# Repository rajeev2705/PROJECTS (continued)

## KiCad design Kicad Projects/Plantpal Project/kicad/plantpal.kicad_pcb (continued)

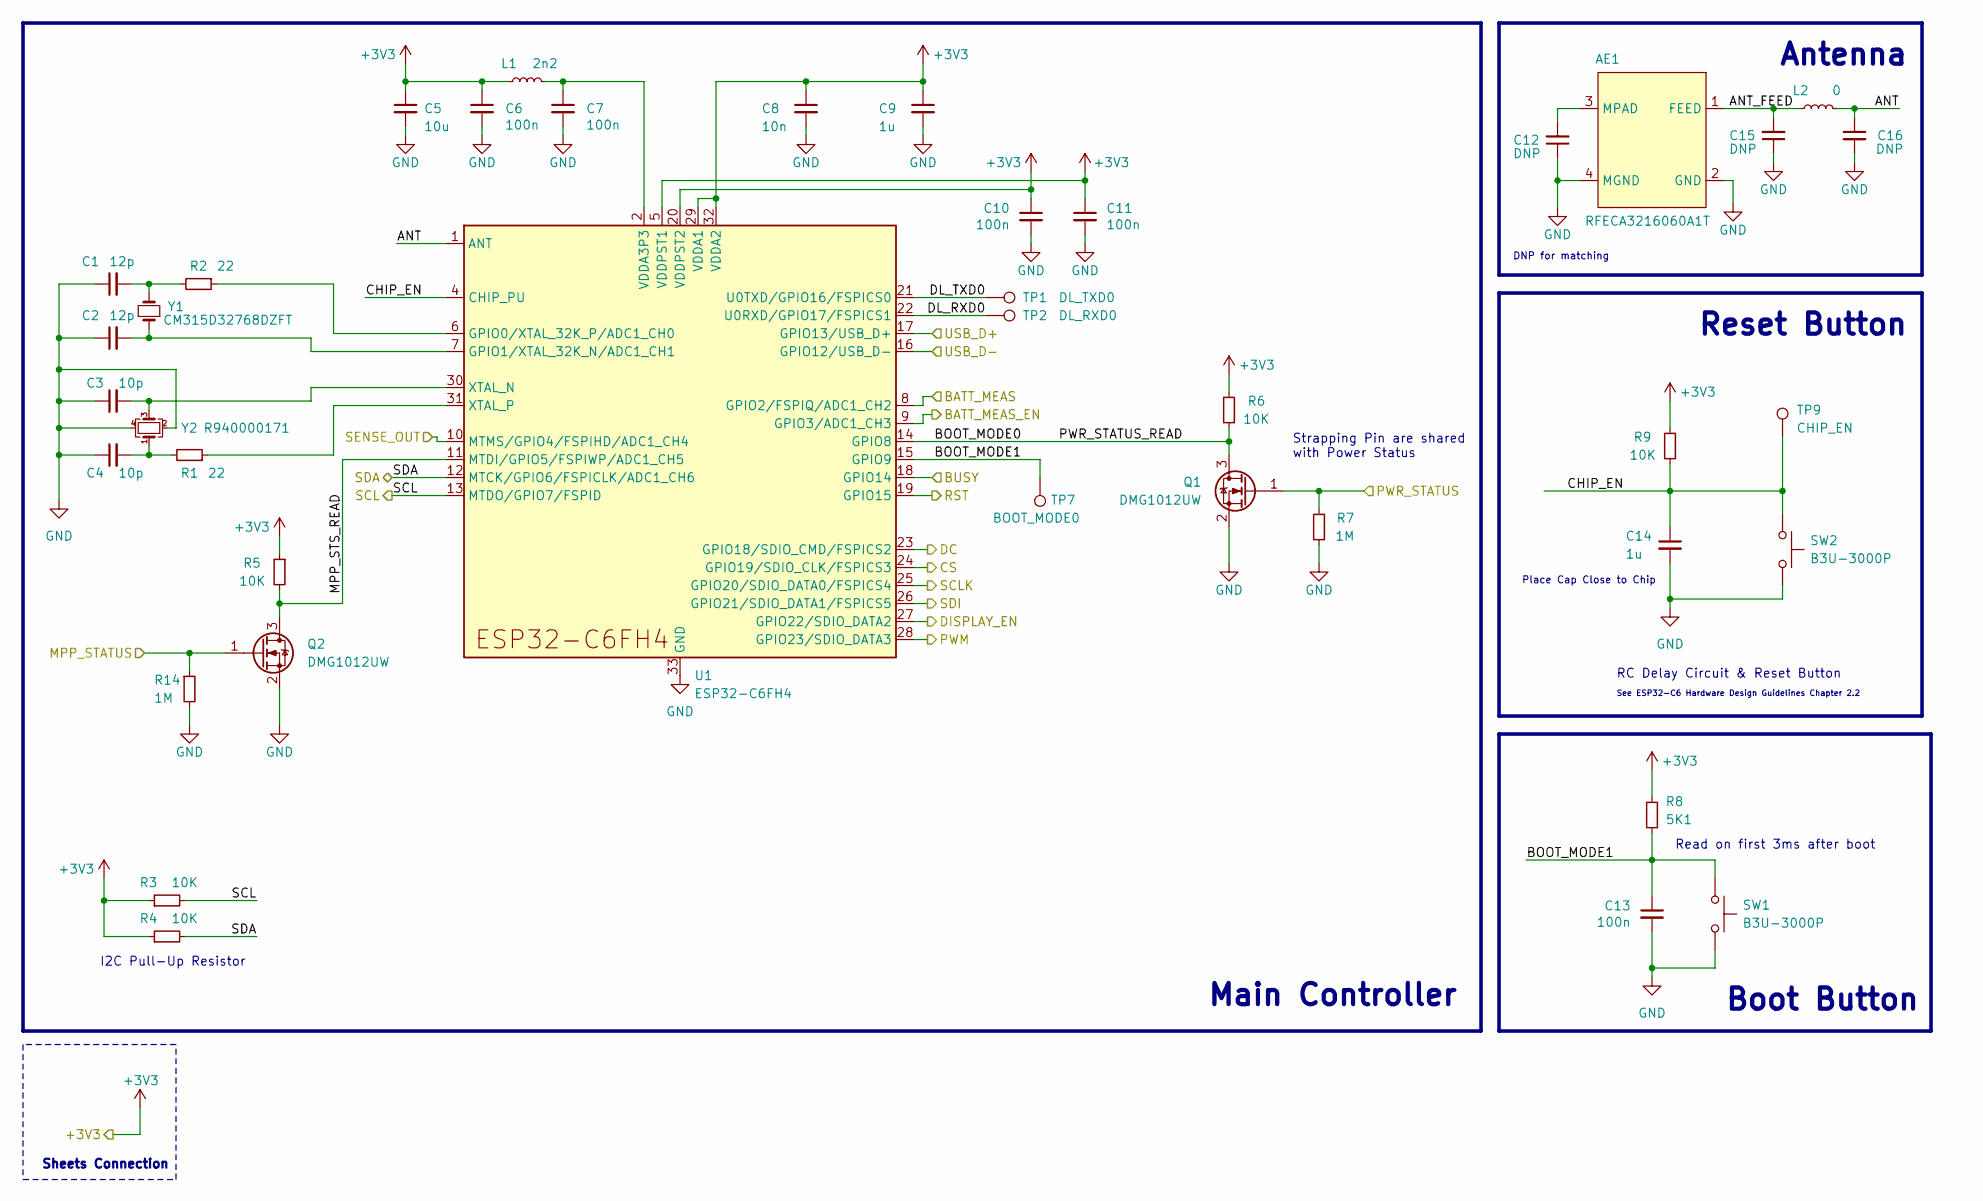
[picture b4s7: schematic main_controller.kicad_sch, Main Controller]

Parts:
AE1: RFECA3216060A1T; Part Description Chip RF Antenna 2.4GHz 2dBi
C1, C2: 12p; C_0402_1005Metric; Part Description Ceramic Capacitors 50V 12pF C0G ±1%
C3, C4: 10p; C_0402_1005Metric; Part Description Ceramic Capacitors 50V 10pF C0G ±1%
C5: 10u; C_0603_1608Metric; Part Description Ceramic Capacitor 10V 10uF X5R ±10% 0603
C6, C7, C10, C11, C13: 100n; C_0402_1005Metric; Part Description Ceramic Capacitor 16V 100nF X7R ±10%
C8: 10n; C_0402_1005Metric; Part Description Ceramic Capacitors 16V 10nF X7R ±10%
C9, C14: 1u; C_0402_1005Metric; Part Description Ceramic Capacitors 10V 1uF X7R ±10%
C12, C15, C16: DNP; C_0402_1005Metric
L1: 2n2; L_0402_1005Metric; Part Description Power Inductors 2.53A 2.2nH ±2%
L2: 0; L_0402_1005Metric; Part Description Resistor 62.5mW ±1% 0Ω
Q1, Q2: DMG1012UW; SOT-323_SC-70; Part Description MOSFET N Channel 20V 1A 450mΩ@4.5V,600m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
R1, R2: 22; R_0402_1005Metric; Part Description Resistor 62.5mW ±1% 22Ω
R3, R4, R5, R6, R9: 10K; R_0402_1005Metric; Part Description Resistors 62.5mW ±1% 10kΩ
R7, R14: 1M; R_0402_1005Metric; Part Description Resistor 62.5mW ±1% 1MΩ
R8: 5K1; R_0402_1005Metric; Part Description Resistor 62.5mW ±1% 5.1kΩ
SW1, SW2: B3U-3000P; SW_SPST_B3U-3000P; Part Description Tactile Switches NO 50mA 100MΩ 12V 1.59N
TP1: DL_TXD0; TestPoint_Pad_D1.0mm
TP2: DL_RXD0; TestPoint_Pad_D1.0mm
TP7: BOOT_MODE0; TestPoint_Pad_D1.0mm
TP9: CHIP_EN; TestPoint_Pad_D1.0mm
U1: ESP32-C6FH4; QFN-32-1EP_5x5mm_P0.5mm_EP3.6x3.6mm; Part Description Wireless SOC Bluetooth, WiFi Bluetooth 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
Y1: CM315D32768DZFT; Crystal_SMD_3215-2Pin_3.2x1.5mm; Part Description Crystals 32.768kHz 12.5pF ±20ppm
Y2: R940000171; Crystal_SMD_2016-4Pin_2.0x1.6mm; Part Description Crystals 40MHz 9pF ±10ppm

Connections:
+3V3: C5.1, C6.1, C8.1, C9.1, C10.1, C11.1, L1.1, R3.1, R4.1, R5.1, R6.1, R8.2, R9.1, U1.5 (VDDPST1), U1.20 (VDDPST2), U1.29 (VDDA1), U1.32 (VDDA2); also elsewhere on the board
/Display/BUSY: U1.18 (GPIO14); also elsewhere on the board
/Display/CS: U1.24 (GPIO19/SDIO_CLK/FSPICS3); also elsewhere on the board
/Display/DC: U1.23 (GPIO18/SDIO_CMD/FSPICS2); also elsewhere on the board
/Display/RST: U1.19 (GPIO15); also elsewhere on the board
/Display/SCLK: U1.25 (GPIO20/SDIO_DATA0/FSPICS4); also elsewhere on the board
/Display/SDI: U1.26 (GPIO21/SDIO_DATA1/FSPICS5); also elsewhere on the board
/Main Controller/ANT: C16.1, L2.2, U1.1 (ANT)
/Main Controller/ANT_FEED: AE1.1 (FEED), C15.2, L2.1
/Main Controller/BATT_MEAS: U1.8 (GPIO2/FSPIQ/ADC1_CH2); also elsewhere on the board
/Main Controller/BATT_MEAS_EN: U1.9 (GPIO3/ADC1_CH3); also elsewhere on the board
/Main Controller/BOOT_MODE0: Q1.3 (D), R6.2, U1.14 (GPIO8)
/Main Controller/BOOT_MODE1: C13.1, R8.1, SW1.1, TP7.1, U1.15 (GPIO9)
/Main Controller/CHIP_EN: C14.1, R9.2, SW2.1, TP9.1, U1.4 (CHIP_PU)
/Main Controller/DISPLAY_EN: U1.27 (GPIO22/SDIO_DATA2); also elsewhere on the board
/Main Controller/DL_RXD0: TP2.1, U1.22 (U0RXD/GPIO17/FSPICS1)
/Main Controller/DL_TXD0: TP1.1, U1.21 (U0TXD/GPIO16/FSPICS0)
/Main Controller/MPP_STATUS: Q2.1 (G), R14.1; also elsewhere on the board
/Main Controller/MPP_STS_READ: Q2.3 (D), R5.2, U1.11 (MTDI/GPIO5/FSPIWP/ADC1_CH5)
/Main Controller/PWM: U1.28 (GPIO23/SDIO_DATA3); also elsewhere on the board
/Main Controller/PWR_STATUS: Q1.1 (G), R7.1; also elsewhere on the board
/Main Controller/SENSE_OUT: U1.10 (MTMS/GPIO4/FSPIHD/ADC1_CH4); also elsewhere on the board
/Main Controller/USB_D+: U1.17 (GPIO13/USB_D+); also elsewhere on the board
/Main Controller/USB_D-: U1.16 (GPIO12/USB_D-); also elsewhere on the board
/SCL: R3.2, U1.13 (MTDO/GPIO7/FSPID); also elsewhere on the board
/SDA: R4.2, U1.12 (MTCK/GPIO6/FSPICLK/ADC1_CH6); also elsewhere on the board
GND: AE1.2 (GND), AE1.4 (MGND), C1.1, C2.1, C3.1, C4.1, C5.2, C6.2, C7.2, C8.2, C9.2, C10.2, C11.2, C12.1, C13.2, C14.2, C15.1, C16.2, Q1.2 (S), Q2.2 (S), R7.2, R14.2, SW1.2, SW2.2, U1.33 (GND), Y2.2, Y2.4; also elsewhere on the board
unnamed: AE1.3 (MPAD), C12.2
unnamed: C1.2, R2.2, Y1.2
unnamed: C4.2, R1.2, Y2.1
unnamed: C7.1, L1.2, U1.2 (VDDA3P3), U1.3 (VDDA3P3)
unnamed: R2.1, U1.6 (GPIO0/XTAL_32K_P/ADC1_CH0)
unnamed: C2.2, U1.7 (GPIO1/XTAL_32K_N/ADC1_CH1), Y1.1
unnamed: C3.2, U1.30 (XTAL_N), Y2.3
unnamed: R1.1, U1.31 (XTAL_P)

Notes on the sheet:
Place Cap Close to Chip
Reset Button
Antenna
DNP for matching
Main Controller
Sheets Connection
Boot Button
See ESP32-C6 Hardware Design Guidelines Chapter 2.2
RC Delay Circuit & Reset Button
Read on first 3ms after boot
I2C Pull-Up Resistor
Strapping Pin are shared with Power Status

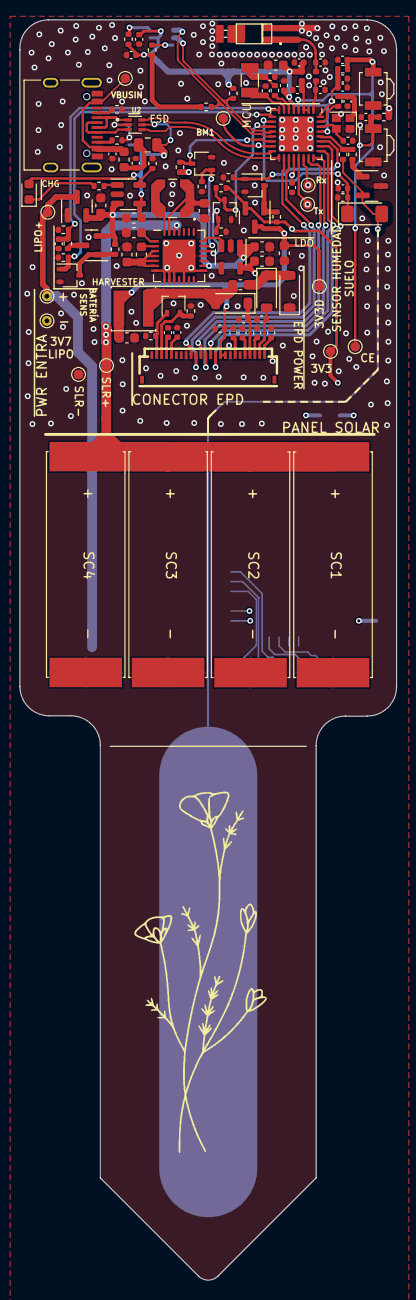
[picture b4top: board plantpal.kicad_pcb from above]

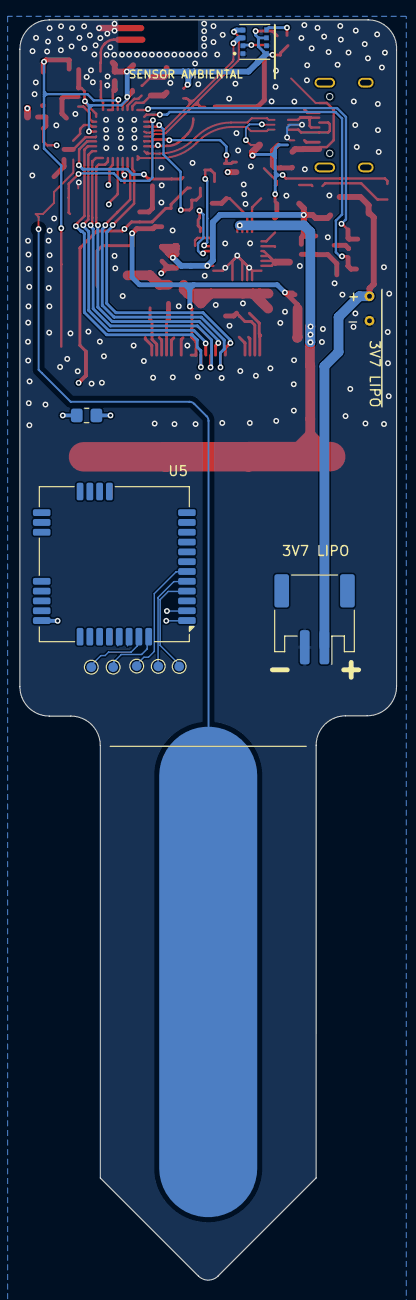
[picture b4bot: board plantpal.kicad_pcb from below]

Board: 4 copper layers, 38.4 x 128.5 mm, 125 parts (8 on the bottom side), 74 nets.

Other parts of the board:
TP12, TP13, TP14, TP15, TP16: TestPoint_Pad_D1.0mm
U5: RAK3172

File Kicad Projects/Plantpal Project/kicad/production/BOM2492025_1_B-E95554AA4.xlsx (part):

BOM File: |  | BOM2492025_1 |  |  |  |  |  |  | Order ID： | B-E95554AA4 |  |  |  | Quote Time: | 2025/09/25 09:05:02
Purchase Quantity： |  | 2 pcs |  |  |  |  |  |  | BOM Total ($)： | 129.17
Inquiry |  |  |  |  |  |  |  |  | HQNextPCB-Quotation
S/N | Designator* | Quantity* | Manufacturer Part Number* | Manufacturer | Package /Footprint | Description | Procurement Type | Customer Note | Quote MPN | Quote Brand | Package /Footprint | Plan Qty | Overage Amount | Quote Qty | Unit Price($) | Subtotal($) | Lead Time | Question from HQ NextPCB | Customer Reply
1 | AE1 | 1 | RFECA3216060A1T | Walsin Technology Corporation | RFECA3216060A1T | RFECA3216060A1T |  |  | RFECA3216060A1T | Walsin | ANT_3.1X1.6MM | 2 | 15 | 17 | 3.5150000000000001E-2 | 0.6 | In Stock
2 | BT1 | 1 | S2B-PH-SM4-TB(LF)(SN) | JST Sales America | JST_PH_S2B-PH-SM4-TB_1x02-1MP_P2.00mm_Horizontal | S2B-PH-SM4-TB(LF)(SN) |  |  | S2B-PH-SM4-TB(LF)(SN) | JST | Accessories_7.9X7.6MM_SM | 2 | 3 | 5 | 0.14524000000000001 | 0.73 | In Stock
3 | C1, C2 | 2 | GCM1555C1H120FA16D | Murata Electronics | 0402_1005Metric | 12p |  |  | GCM1555C1H120FA16D | Murata | 0402 | 4 | 50 | 54 | 7.8100000000000001E-3 | 0.42 | In Stock
4 | C3, C4 | 2 | GRM1555C1H100FA01D | Murata Electronics | 0402_1005Metric | 10p |  |  | GRM1555C1H100FA01D | Murata | 0402 | 4 | 50 | 54 | 8.0599999999999995E-3 | 0.44 | In Stock
5 | C5, C19, C20, C23, C24, C25, C26 | 7 | CL10A106KP8NNNC | Samsung Electro-Mechanics | 0603_1608Metric | 10u |  |  | CL10A106KP8NNNC | Samsung | 0603 | 14 | 40 | 54 | 4.7499999999999999E-3 | 0.26 | In Stock
6 | C6, C7, C10, C11, C13, C27, C28, C29 | 8 | CL05B104KO5NNNC | Samsung Electro-Mechanics | 0402_1005Metric | 100n |  |  | CL05B104KO5NNNC | Samsung | 0402 | 16 | 50 | 100 | 8.4999999999999995E-4 | 0.09 | In Stock
7 | C8 | 1 | CC0402KRX7R7BB103 | YAGEO | 0402_1005Metric | 10n |  |  | CC0402KRX7R7BB103 | Yageo | 0402 | 2 | 50 | 100 | 6.6E-4 | 7.0000000000000007E-2 | In Stock
8 | C9, C14, C31, C32, C33, C34, C35, C36, C37, C38, C39 | 11 | GRM155Z71A105KE01D | Murata Electronics | 0402_1005Metric | 1u |  |  | GRM155Z71A105KE01D | Murata | 0402 | 22 | 50 | 72 | 1.2030000000000001E-2 | 0.87 | In Stock
9 | C17 | 1 | CC0402KRX7R7BB103 | YAGEO | 0402_1005Metric | 10n |  |  | CC0402KRX7R7BB103 | Yageo | 0402 | 2 | 50 | 100 | 6.6E-4 | 7.0000000000000007E-2 | In Stock
10 | C18 | 1 | CL05B104KO5NNNC | Samsung Electro-Mechanics | 0402_1005Metric | 100n |  |  | CL05B104KO5NNNC | Samsung | 0402 | 2 | 50 | 100 | 8.4999999999999995E-4 | 0.09 | In Stock
11 | C21, C22 | 2 | GRM188R61A226ME15D | Murata Electronics | 0603_1608Metric | 22u |  |  | GRM188R61A226ME15D | Murata | 0603 | 4 | 40 | 100 | 1.2370000000000001E-2 | 1.24 | In Stock
12 | C30 | 1 | CL05B102KB5NNNC | Samsung Electro-Mechanics | 0402_1005Metric | 1n |  |  | CL05B102KB5NNNC | Samsung | 0402 | 2 | 50 | 52 | 8.7000000000000001E-4 | 0.05 | In Stock
13 | C40, C41 | 2 | CL10A475KA8NQNC | Samsung Electro-Mechanics | 0603_1608Metric | 4u7 |  |  | CL10A475KA8NQNC | Samsung | 0603 | 4 | 40 | 44 | 1.255E-2 | 0.55000000000000004 | In Stock
14 | D1 | 1 | VLMO1300-GS08 | Vishay Intertech | 0603_1608Metric | VLMO1300-GS08 |  |  | VLMO1300-GS08 | Vishay Semiconductors | 0603 | 2 | 15 | 17 | 0.16650000000000001 | 2.83 | 7-18 Days
15 | D3 | 1 | LL4148 | ST(Semtech) | MiniMELF | LL4148 |  |  | LL4148 | YONGYUTAI | SOD80 | 2 | 15 | 17 | 4.3400000000000001E-3 | 7.0000000000000007E-2 | In Stock
16 | D4, D5, D6 | 3 | MBR0530T1G | onsemi | SOD-123 | MBR0530 |  |  | MBR0530T1G | ON | SOD-123 | 6 | 30 | 36 | 2.826E-2 | 1.02 | In Stock
17 | F1 | 1 | SMD0805P075TF | RUILON(Shenzhen Ruilongyuan Elec) | 0805_2012Metric | 0.75A |  |  | SMD0805P075TF | RUILON(瑞隆源) | 0805 | 2 | 15 | 17 | 8.1909999999999997E-2 | 1.39 | 4-7 Days
18 | FB1 | 1 | MMZ1608B601CTAH0 | TDK | 0603_1608Metric | MMZ1608B601CTAH0 |  |  | MMZ1608B601CTAH0 | TDK | 0603 | 2 | 40 | 42 | 1.1730000000000001E-2 | 0.49 | In Stock
19 | J1 | 1 | U262-161N-4BVC11 | XKB Connectivity | XKB_U262-16XN-4BVC11 | U262-161N-4BVC11 |  |  | U262-161N-4BVC11 | XKB | SMD | 2 | 3 | 5 | 0.24346000000000001 | 1.22 | In Stock
20 | J4 | 1 | HC-FPC-05-09-24RLTAG | HCTL | FPC-SMD_24P-P0.50_HC-FPC-05-09-24RLTAG | HC-FPC-05-09-24RLTAG |  |  | HC-FPC-05-09-24RLTAG | HCTL | SMD,P=0.5mm,卧贴 | 2 | 3 | 5 | 0.14030000000000001 | 0.7 | In Stock
21 | L1 | 1 | LQW15AN2N2G80D | Murata Electronics | 0402_1005Metric | 2n2 |  |  | LQW15AN2N2G80D | muRata(村田) | 0402 | 2 | 40 | 42 | 6.3049999999999995E-2 | 2.65 | 4-7 Days
22 | L2 | 1 | 0402WGF0000TCE | UNI-ROYAL(Uniroyal Elec) | 0402_1005Metric |  |  |  | 0402WGF0000TCE | Uniohm | 0402 | 2 | 50 | 100 | 3.1E-4 | 0.03 | In Stock
23 | L3 | 1 | LPS4012-103MRC | Coilcraft | LPS4012-103MRB | 10u 0.55A |  |  | LPS4012-103MRC | Coilcraft(线艺) | SMD,3.9x3.9mm | 2 | 2 | 4 | 0.64856000000000003 | 2.59 | 4-7 Days
24 | L4 | 1 | MLZ1608M100WT000 | TDK | 0603_1608Metric | 10u |  |  | MLZ1608M100WT000 | TDK | 0603 | 2 | 30 | 32 | 3.5150000000000001E-2 | 1.1200000000000001 | In Stock
25 | L5 | 1 | FNR4012S100MT | cjiang (Changjiang Microelectronics Tech) | FNR4012S | 10u 1A |  |  | FNR4012S100MT | cjiang(长江微电) | 4012 | 2 | 5 | 10 | 5.6829999999999999E-2 | 0.56999999999999995 | 4-7 Days
26 | Q1, Q2, Q5, Q9 | 4 | DMG1012UW-7 | Diodes Incorporated | SOT-323_SC-70 | DMG1012UW |  |  | DMG1012UW-7 | DIODES | SOT-323 | 8 | 15 | 23 | 3.4430000000000002E-2 | 0.79 | In Stock
27 | Q3 | 1 | MMBT3906 2A | Jiangsu Changjing Electronics Technology Co., Ltd. | SOT-23 | MMBT3906 |  |  | MMBT3906 2A | TDSEMIC | SOT-23 | 2 | 15 | 50 | 3.0100000000000001E-3 | 0.15 | In Stock
28 | Q4, Q8 | 2 | PMV32UP | TECH PUBLIC | SOT-23 | PMV32UP |  |  | PMV32UP | TECH PUBLIC(台舟) | SOT-23 | 4 | 10 | 14 | 8.9779999999999999E-2 | 1.26 | 4-7 Days
29 | Q6 | 1 | AO3407A | Alpha & Omega Semicon | SOT-23 | AO3407A |  |  | AO3407A | BY | SOT23-3 | 2 | 15 | 17 | 2.554E-2 | 0.43 | In Stock
30 | Q7 | 1 | SI1308EDL-T1-GE3 | Vishay Intertech | SOT-323_SC-70 | SI1308EDL |  |  | SI1308EDL-T1-GE3 | Vishay | SOT-323 | 2 | 10 | 12 | 0.11650000000000001 | 1.4 | In Stock
31 | R1, R2 | 2 | 0402WGF220JTCE | UNI-ROYAL(Uniroyal Elec) | R_0402_1005Metric | 22 |  |  | 0402WGF220JTCE | Uniohm | 0402 | 4 | 50 | 100 | 3.1E-4 | 0.03 | In Stock
32 | R3, R4, R5, R6, R9, R16, R17, R18, R19, R21 | 10 | 0402WGF1002TCE | UNI-ROYAL(Uniroyal Elec) | R_0402_1005Metric | 10K |  |  | 0402WGF1002TCE | Uniohm | 0402 | 20 | 50 | 100 | 3.3E-4 | 0.03 | In Stock
33 | R7, R14, R22, R23, R24, R26, R28, R29 | 8 | 0402WGF1004TCE | UNI-ROYAL(Uniroyal Elec) | R_0402_1005Metric | 1M |  |  | 0402WGF1004TCE | Uniohm | 0402 | 16 | 50 | 100 | 2.9999999999999997E-4 | 0.03 | In Stock
34 | R8, R10, R11 | 3 | 0402WGF5101TCE | UNI-ROYAL(Uniroyal Elec) | R_0402_1005Metric | 5K1 |  |  | 0402WGF5101TCE | Uniohm | 0402 | 6 | 50 | 100 | 2.9E-4 | 0.03 | In Stock
35 | R12 | 1 | 0402WGF2001TCE | UNI-ROYAL(Uniroyal Elec) | R_0402_1005Metric | 2K |  |  | 0402WGF2001TCE | Uniohm | 0402 | 2 | 50 | 100 | 3.3E-4 | 0.03 | In Stock
36 | R13 | 1 | 0402WGF1001TCE | UNI-ROYAL(Uniroyal Elec) | R_0402_1005Metric | 1K |  |  | 0402WGF1001TCE | Uniohm | 0402 | 2 | 50 | 100 | 3.4000000000000002E-4 | 0.03 | In Stock
37 | R20 | 1 | 0402WGF4701TCE | UNI-ROYAL(Uniroyal Elec) | R_0402_1005Metric | 4K7 |  |  | 0402WGF4701TCE | Uniohm | 0402 | 2 | 50 | 100 | 3.3E-4 | 0.03 | In Stock
38 | R25 | 1 | RCWE0402R470FKEA | Vishay Intertech | R_0402_1005Metric | 470m |  |  | RCWE0402R470FKEA | Vishay / Dale | 0402 | 2 | 35 | 37 | 0.14219000000000001 | 5.26 | 7-18 Days
39 | SC1, SC2, SC3, SC4 | 4 | KXOB25-05X3F-TR | ANYSOLAR Ltd | KXOB25-05X3F-TR | KXOB25-05X3F-TR |  |  | KXOB25-05X3F-TR | ANYSOLAR Ltd | SMD_8X23 | 8 | 1 | 9 | 4.0199999999999996 | 36.18 | 7-18 Days
40 | SW1, SW2 | 2 | B3U-3000P | Omron Electronics | B3U-3000P | B3U-3000P |  |  | B3U-3000P | OMRON | SMD | 4 | 3 | 7 | 0.13292000000000001 | 0.93 | 4-7 Days
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
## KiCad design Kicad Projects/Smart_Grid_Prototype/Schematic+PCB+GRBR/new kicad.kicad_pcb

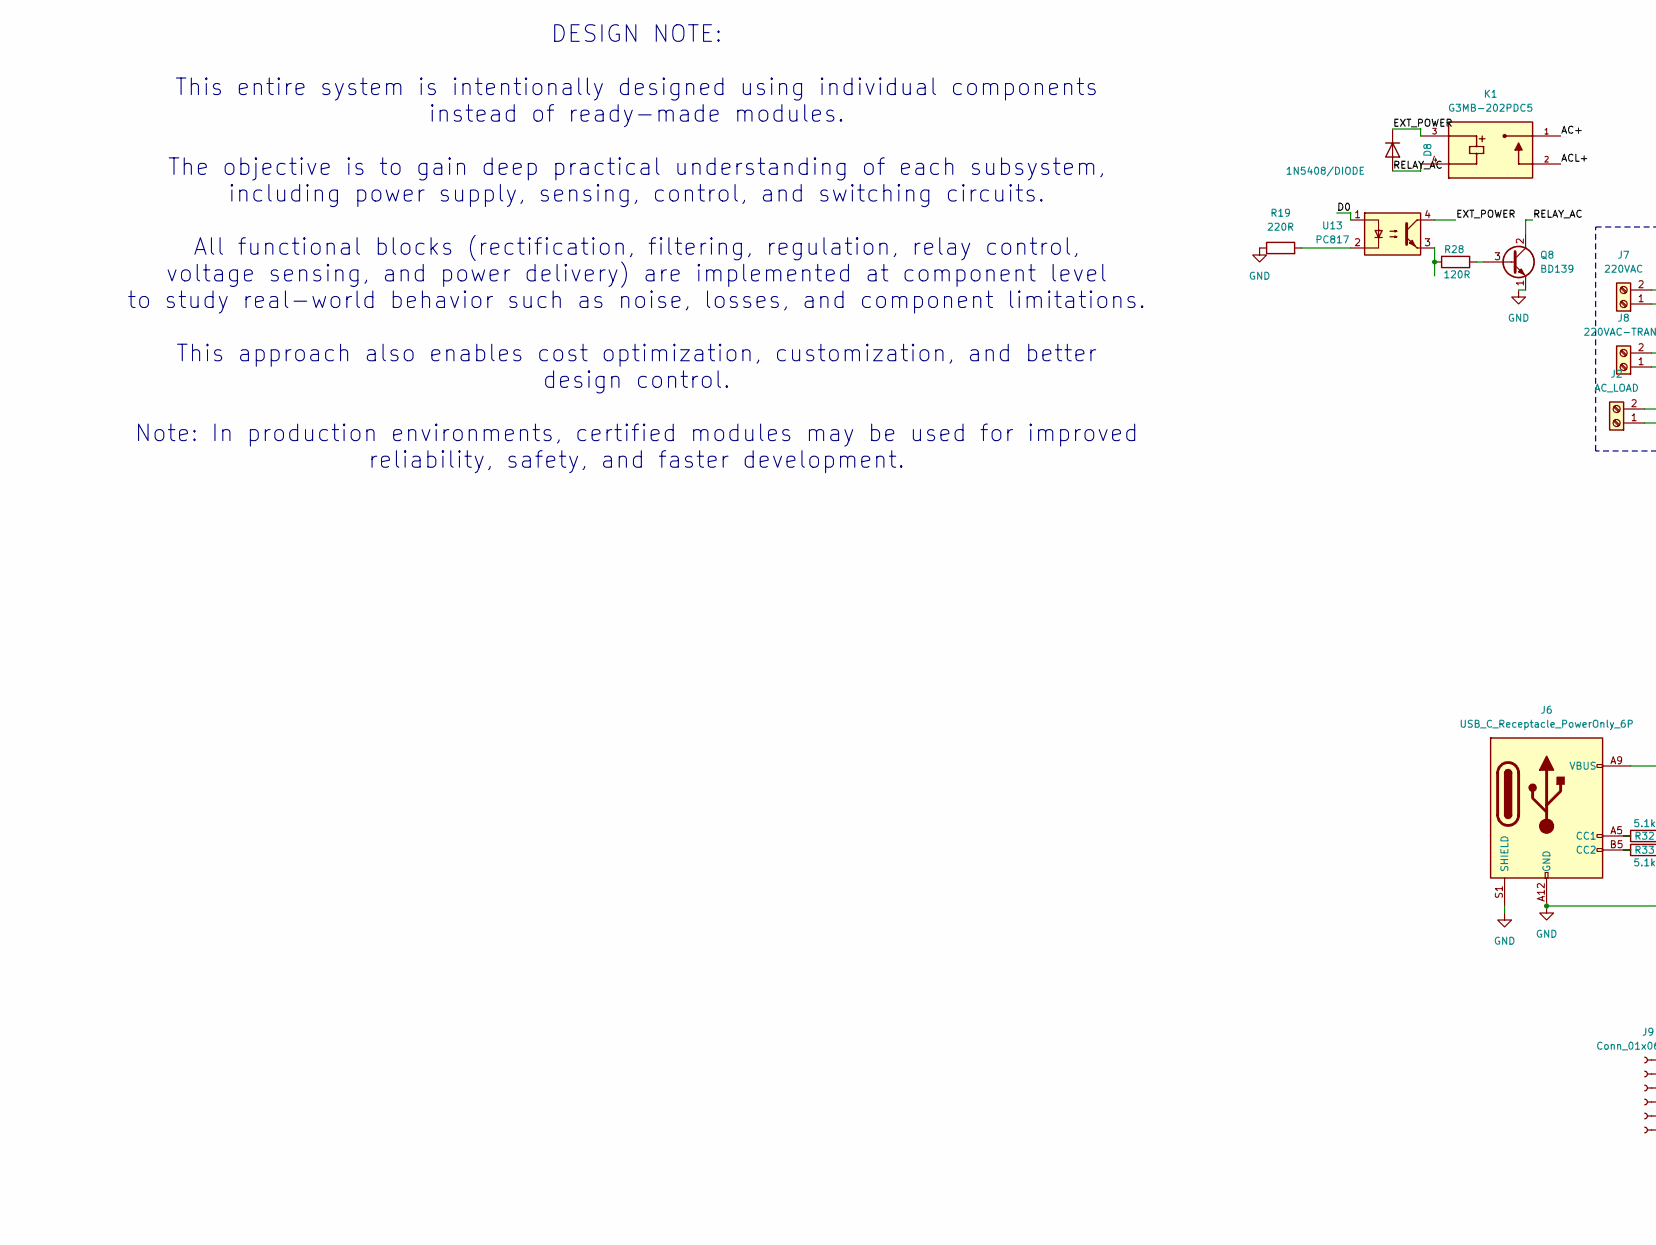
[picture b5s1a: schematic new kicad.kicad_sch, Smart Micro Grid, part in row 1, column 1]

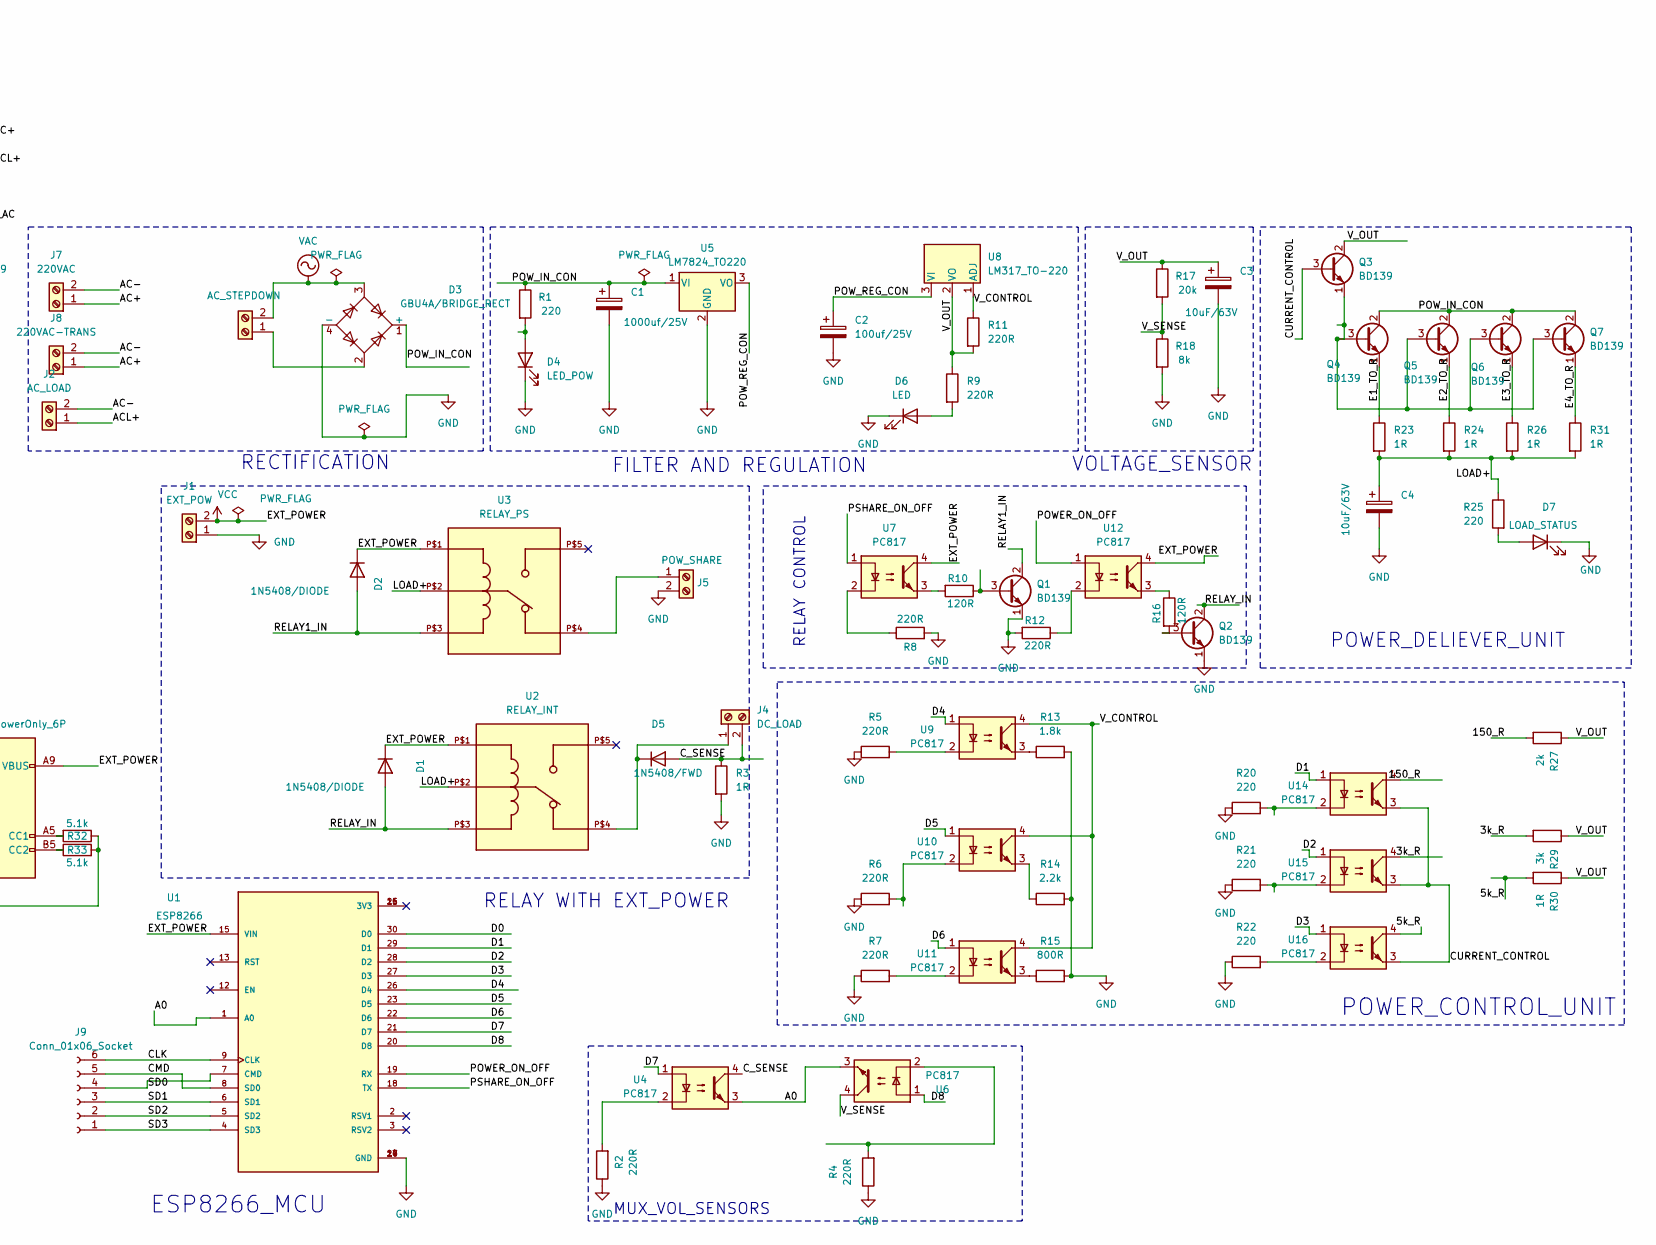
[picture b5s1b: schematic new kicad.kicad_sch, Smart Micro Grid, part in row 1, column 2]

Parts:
C1: 1000uf/25V; CP_Radial_D10.0mm_P5.00mm
C2: 100uf/25V; CP_Radial_D10.0mm_P5.00mm
C3, C4: 10uF/63V; CP_Radial_D5.0mm_P2.50mm
D1, D2, D8: 1N5408/DIODE; D_5W_P12.70mm_Horizontal
D3: GBU4A/BRIDGE_RECT; Diode_Bridge_Vishay_GBU
D4: LED_POW; LED_D5.0mm
D5: 1N5408/FWD; D_5W_P12.70mm_Horizontal
D6: LED; LED_D5.0mm
D7: LOAD_STATUS; LED_D5.0mm
J1: EXT_POW; TerminalBlock_4Ucon_1x02_P3.50mm_Horizontal
J2: AC_LOAD; TerminalBlock_4Ucon_1x02_P3.50mm_Horizontal
J3: AC_STEPDOWN; TerminalBlock_4Ucon_1x02_P3.50mm_Horizontal
J4: DC_LOAD; TerminalBlock_4Ucon_1x02_P3.50mm_Horizontal
J5: POW_SHARE; TerminalBlock_4Ucon_1x02_P3.50mm_Horizontal
J6: USB_C_Receptacle_PowerOnly_6P; USB_C_Receptacle_GCT_USB4125-xx-x-0190_6P_TopMnt_Horizontal
J7: 220VAC; TerminalBlock_4Ucon_1x02_P3.50mm_Horizontal
J8: 220VAC-TRANS; TerminalBlock_4Ucon_1x02_P3.50mm_Horizontal
J9: Conn_01x06_Socket; PinHeader_1x06_P2.54mm_Vertical
K1: G3MB-202PDC5; RELAY_G3MB-202PDC5; PARTREV J091-E1-1A
Q1, Q2, Q3, Q4, Q5, Q6, Q7, Q8: BD139; TO-126-3_Vertical
R1, R20, R21, R22, R25: 220; R_Axial_DIN0207_L6.3mm_D2.5mm_P15.24mm_Horizontal
R2, R4, R5, R6, R7, R8, R9, R11, R12, R19: 220R; R_Axial_DIN0207_L6.3mm_D2.5mm_P15.24mm_Horizontal
R3: 1R; R_Axial_DIN0617_L17.0mm_D6.0mm_P25.40mm_Horizontal
R10, R16, R28: 120R; R_Axial_DIN0207_L6.3mm_D2.5mm_P15.24mm_Horizontal
R13: 1.8k; R_Axial_DIN0207_L6.3mm_D2.5mm_P15.24mm_Horizontal
R14: 2.2k; R_Axial_DIN0207_L6.3mm_D2.5mm_P15.24mm_Horizontal
R15: 800R; R_Axial_DIN0207_L6.3mm_D2.5mm_P15.24mm_Horizontal
R17: 20k; R_Axial_DIN0207_L6.3mm_D2.5mm_P15.24mm_Horizontal
R18: 8k; R_Axial_DIN0207_L6.3mm_D2.5mm_P15.24mm_Horizontal
R23, R24, R26, R31: 1R; R_Axial_Power_L20.0mm_W6.4mm_P30.48mm
R27: 2k; R_Axial_DIN0207_L6.3mm_D2.5mm_P15.24mm_Horizontal
R29: 3k; R_Axial_DIN0207_L6.3mm_D2.5mm_P15.24mm_Horizontal
R30: 1R; R_Axial_DIN0207_L6.3mm_D2.5mm_P15.24mm_Horizontal
R32, R33: 5.1k; R_Axial_DIN0207_L6.3mm_D2.5mm_P15.24mm_Horizontal
U1: ESP8266; MODULE_ZC563900; PARTREV 1.0
U2: RELAY_INT; J107F
U3: RELAY_PS; J107F
U4, U6, U7, U9, U10, U11, U12, U13, U14, U15, U16: PC817; DIP-4_W7.62mm
U5: LM7824_TO220; TO-220-3_Vertical
U8: LM317_TO-220; TO-220-3_Vertical

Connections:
/3k_R: R29.2, U15.4
/5k_R: R30.2, U16.4
/150_R: R27.2, U14.4
/A0: U1.1 (A0), U4.3, U6.3
/AC+: J7.1, J8.1, K1.1
/AC-: J2.2, J7.2, J8.2
/ACL+: J2.1, K1.2
/CLK: J9.6, U1.9 (CLK)
/CMD: J9.5, U1.8 (SD0)
/CURRENT_CONTROL: Q3.3 (B), U14.3, U15.3, U16.3
/C_SENSE: D5.2 (A), J4.2, R3.1, U4.4
/D0: U1.30 (D0), U13.1
/D1: U1.29 (D1), U14.1
/D2: U1.28 (D2), U15.1
/D3: U1.27 (D3), U16.1
/D4: U1.26 (D4), U9.1
/D5: U1.23 (D5), U10.1
/D6: U1.22 (D6), U11.1
/D7: U1.21 (D7), U4.1
/D8: U1.20 (D8), U6.1
/E1_TO_R: Q4.1 (E), R23.1
/E2_TO_R: Q5.1 (E), R24.1
/E3_TO_R: Q6.1 (E), R26.1
/E4_TO_R: Q7.1 (E), R31.1
/LOAD+: C4.1, R23.2, R24.2, R25.1, R26.2, R31.2, U2.P$2, U3.P$2
/POWER_ON_OFF: U1.19 (RX), U12.1
/POW_IN_CON: C1.1, D3.1 (+), Q4.2 (C), Q5.2 (C), Q6.2 (C), Q7.2 (C), R1.1, U5.1 (VI)
/POW_REG_CON: C2.1, U5.3 (VO), U8.3 (VI)
/PSHARE_ON_OFF: U1.18 (TX), U7.1
/RELAY1_IN: D2.2 (A), Q1.2 (C), U3.P$3
/RELAY_AC: D8.2 (A), K1.4, Q8.2 (C)
/RELAY_IN: D1.2 (A), Q2.2 (C), U2.P$3
/SD0: J9.4, U1.7 (CMD)
/SD1: J9.3, U1.6 (SD1)
/SD2: J9.2, U1.5 (SD2)
/SD3: J9.1, U1.4 (SD3)
/V_CONTROL: R11.1, U8.1 (ADJ), U9.4, U10.4, U11.4
/V_OUT: C3.1, Q3.2 (C), R9.1, R11.2, R17.1, R27.1, R29.1, R30.1, U8.2 (VO)
/V_SENSE: R17.2, R18.1, U6.4
GND: C1.2, C2.2, C3.2, C4.2, D3.4 (-), D4.1 (K), D6.1 (K), D7.1 (K), J1.1, J5.2, J6.A12 (GND), J6.B12 (GND), J6.S1 (SHIELD), Q1.1 (E), Q2.1 (E), Q8.1 (E), R2.1, R3.2, R4.1, R5.1, R6.1, R7.1, R8.2, R12.2, R13.2, R14.2, R15.2, R18.2, R19.1, R20.1, R21.1, R22.1, R32.1, R33.2, U1.10 (GND), U1.14 (GND), U1.17 (GND), U1.24 (GND), U5.2 (GND)
unnamed: D4.2 (A), R1.2
unnamed: D5.1 (K), J4.1, U2.P$4
unnamed: D6.2 (A), R9.2
unnamed: D7.2 (A), R25.2
unnamed: D3.2, J3.1
unnamed: J5.1, U3.P$4
unnamed: J6.A5 (CC1), R32.2
unnamed: J6.B5 (CC2), R33.1
unnamed: Q1.3 (B), R10.1
unnamed: Q2.3 (B), R16.2
unnamed: Q3.1 (E), Q4.3 (B), Q5.3 (B), Q6.3 (B), Q7.3 (B)
unnamed: Q8.3 (B), R28.1
unnamed: R2.2, U4.2
unnamed: R4.2, U6.2
unnamed: R5.2, U9.2
unnamed: R6.2, U10.2
unnamed: R7.2, U11.2
unnamed: R8.1, U7.2
unnamed: R10.2, U7.3
unnamed: R12.1, U12.2
unnamed: R13.1, U9.3
unnamed: R14.1, U10.3
unnamed: R15.1, U11.3
unnamed: R16.1, U12.3
unnamed: R19.2, U13.2
unnamed: R20.2, U14.2
unnamed: R21.2, U15.2
unnamed: R22.2, U16.2
unnamed: R28.2, U13.3
VAC: D3.3, J3.2
VCC: D1.1 (K), D2.1 (K), D8.1 (K), J1.2, J6.A9 (VBUS), J6.B9 (VBUS), K1.3, U1.15 (VIN), U2.P$1, U3.P$1, U7.4, U12.4, U13.4

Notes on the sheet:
RELAY WITH EXT_POWER
ESP8266_MCU
RECTIFICATION
VOLTAGE_SENSOR
POWER_DELIEVER_UNIT
RELAY CONTROL
FILTER AND REGULATION
MUX_VOL_SENSORS
POWER_CONTROL_UNIT
DESIGN NOTE: This entire system is intentionally designed using individual components instead of ready-made modules. The objective is to gain deep practical understanding of each subsystem, including power supply, sensing, control, and switching circuits. All functional blocks (rectification, filte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

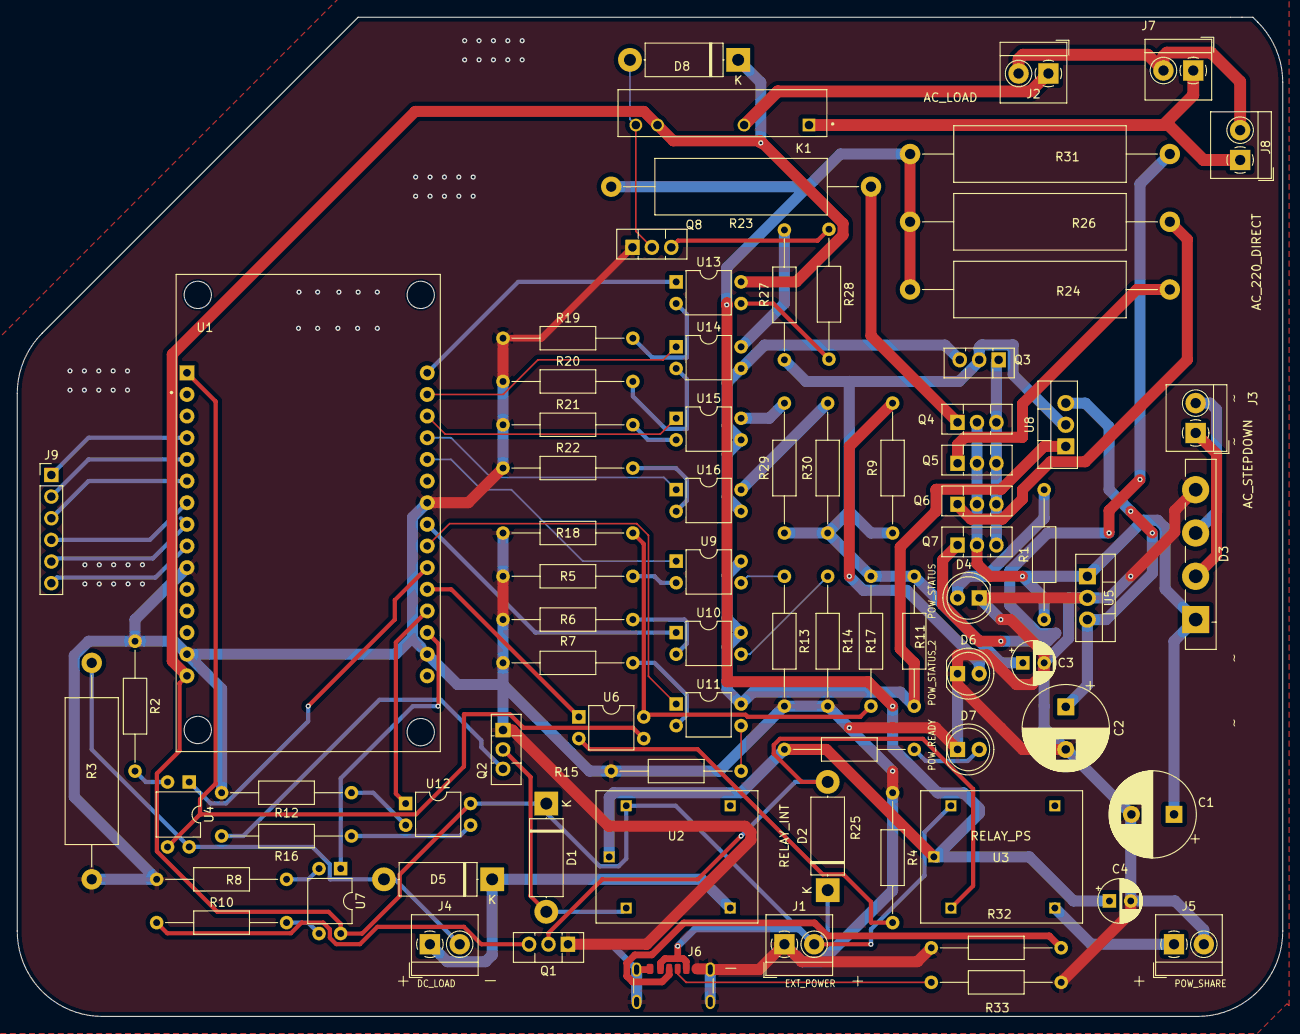
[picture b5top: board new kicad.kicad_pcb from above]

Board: 2 copper layers, 148.5 x 117.2 mm, 79 parts (0 on the bottom side), 71 nets.
